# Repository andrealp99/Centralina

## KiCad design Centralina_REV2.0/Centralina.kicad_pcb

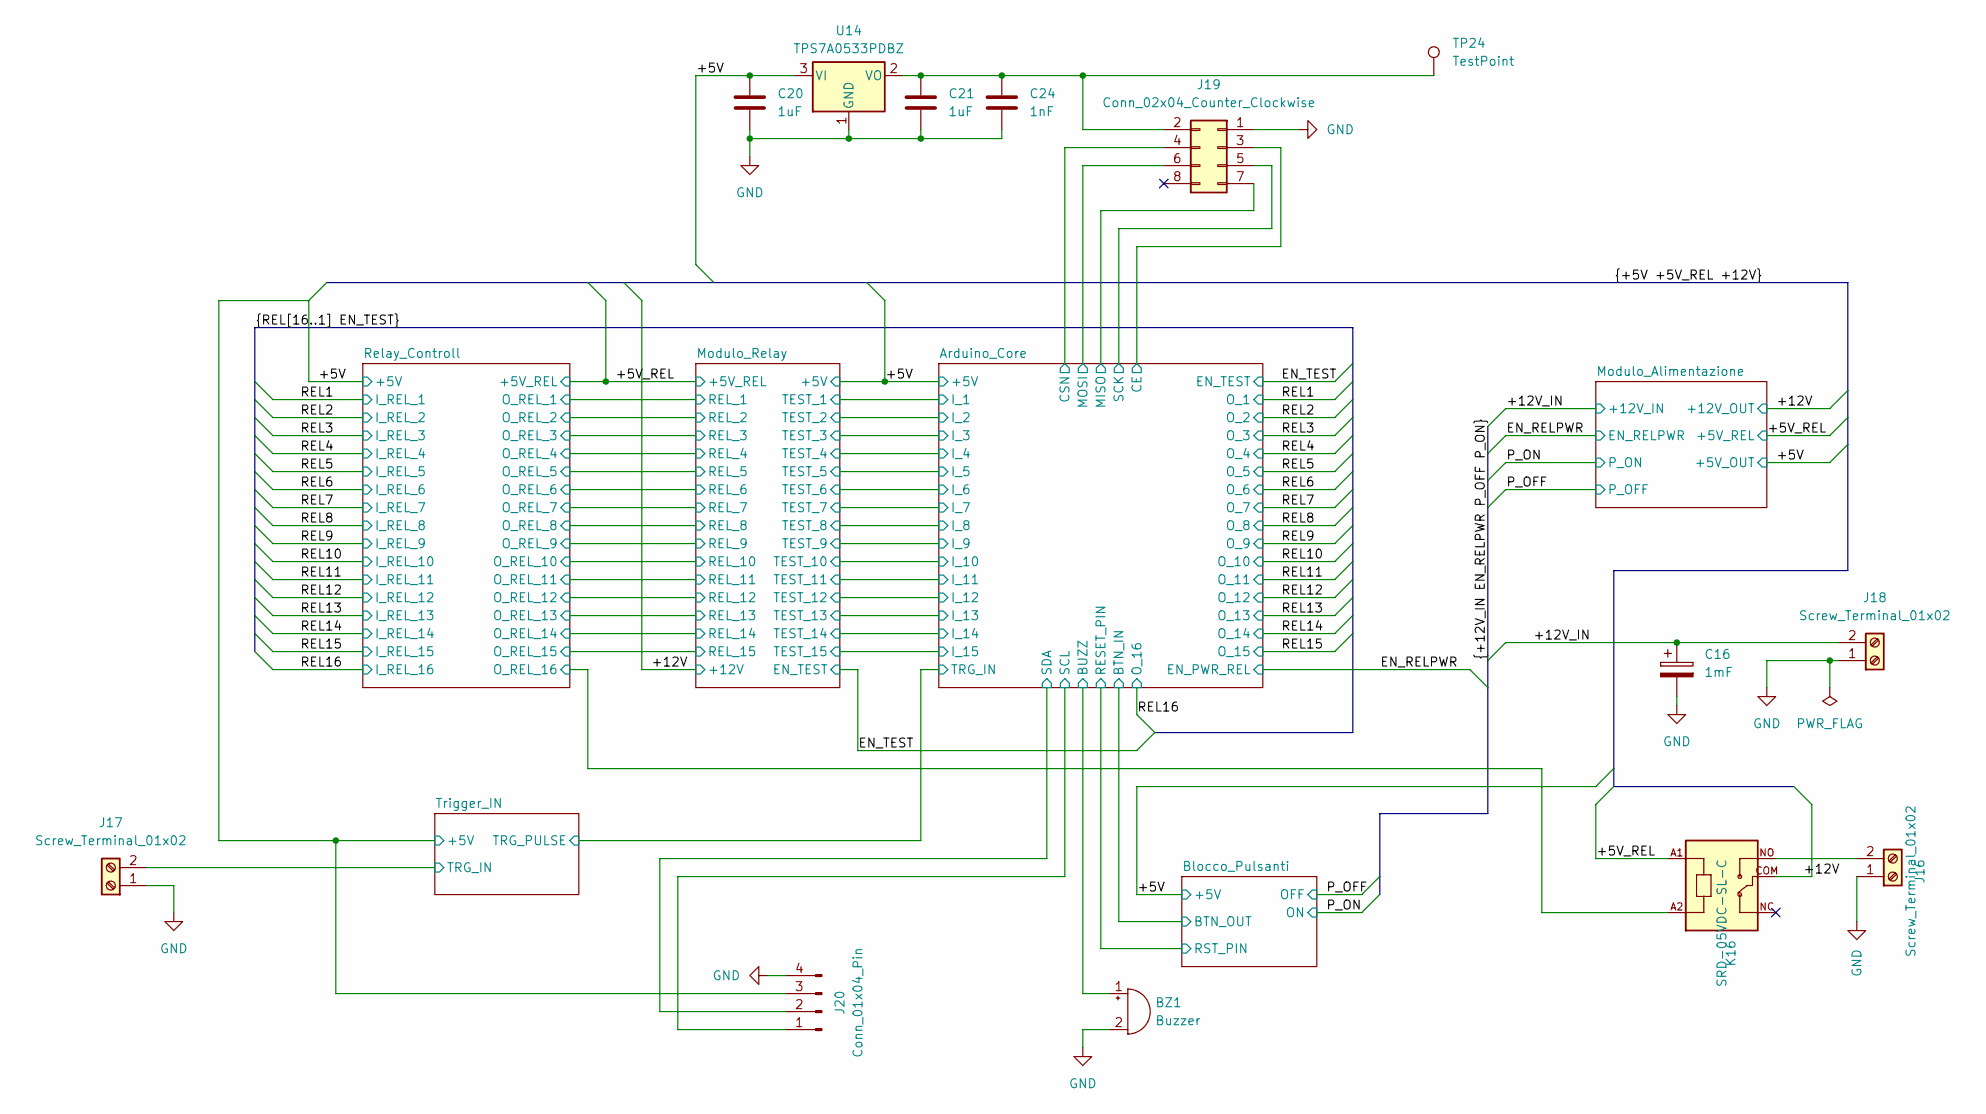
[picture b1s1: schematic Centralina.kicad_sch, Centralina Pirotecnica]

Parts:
BZ1: Buzzer; BUZ-TH_BD9.0-P4.00-D0.6-FD
C16: 1mF; CP_Radial_D10.0mm_P5.00mm
C20, C21: 1uF; C_0805_2012Metric
C24: 1nF; C_0805_2012Metric
J16, J17, J18: Screw_Terminal_01x02; mors_2p
J19: Conn_02x04_Counter_Clockwise; HDR-TH_8P-P2.54-V-F-R2-C4-S2.54
J20: Conn_01x04_Pin; HDR-TH_4P-P2.54-H-F-W10.2
K16: SRD-05VDC-SL-C; RELAY_SRD-05VDC-SL-C
TP24: TestPoint; TestPoint_Pad_D1.0mm
U14: TPS7A0533PDBZ; SOT-23

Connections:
/+5V: C20.1, J20.3, U14.3 (VI); also elsewhere on the board
/+5V_REL: K16.A1; also elsewhere on the board
/+12V: K16.COM; also elsewhere on the board
/+12V_IN: C16.1, J18.2; also elsewhere on the board
/Arduino_Core/BUZZ: BZ1.1 (+); also elsewhere on the board
/Arduino_Core/CE: J19.3 (Pin_2); also elsewhere on the board
/Arduino_Core/CSN: J19.4 (Pin_7); also elsewhere on the board
/Arduino_Core/MISO: J19.7 (Pin_4); also elsewhere on the board
/Arduino_Core/MOSI: J19.6; also elsewhere on the board
/Arduino_Core/SCK: J19.5 (Pin_3); also elsewhere on the board
/Arduino_Core/SCL: J20.1; also elsewhere on the board
/Arduino_Core/SDA: J20.2; also elsewhere on the board
/Relay_Controll/O_REL_16: K16.A2; also elsewhere on the board
/Trigger_IN/TRG_IN: J17.2; also elsewhere on the board
GND: BZ1.2 (-), C16.2, C20.2, C21.2, C24.2, J16.1, J17.1, J18.1, J19.1, J20.4, U14.1 (GND); also elsewhere on the board
unnamed: J16.2, K16.NO
unnamed: C21.1, C24.1, J19.2 (Pin_8), TP24.1, U14.2 (VO)

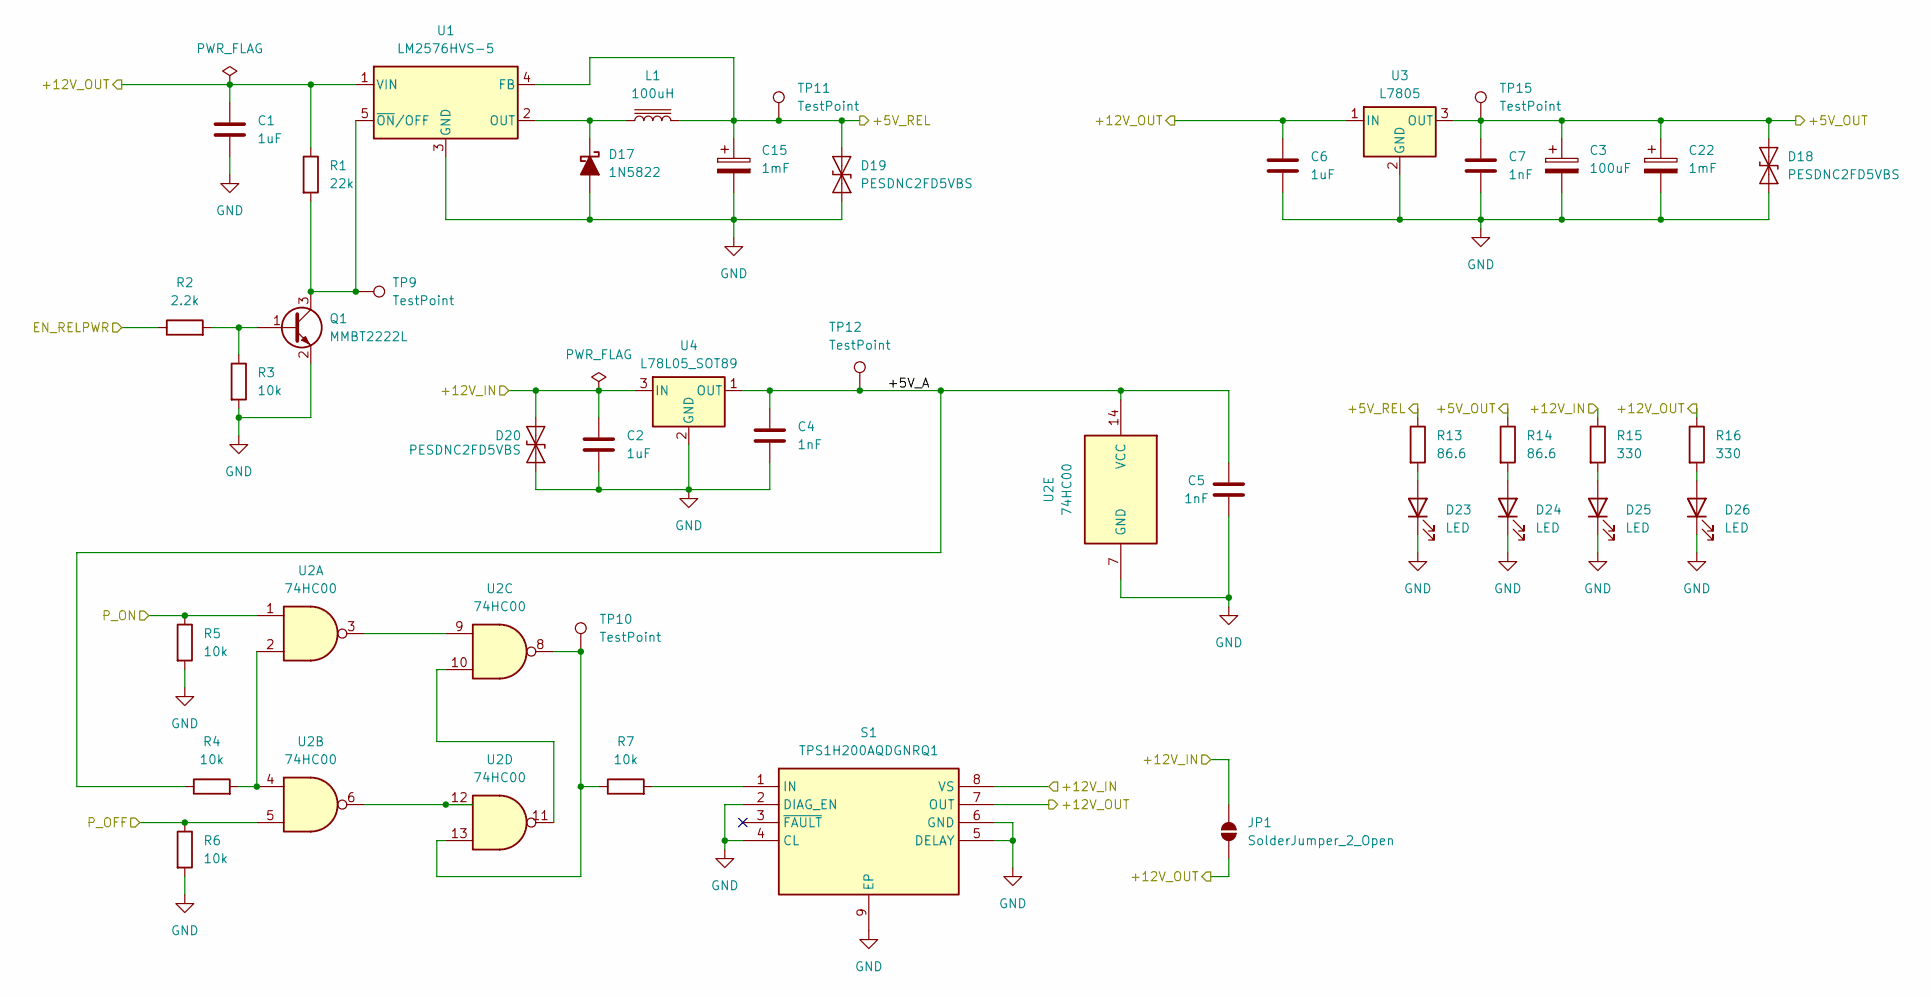
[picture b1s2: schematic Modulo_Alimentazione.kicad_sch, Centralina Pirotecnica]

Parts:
C1, C2, C6: 1uF; C_0805_2012Metric
C3: 100uF; CP_Radial_D5.0mm_P2.00mm
C4, C5, C7: 1nF; C_0805_2012Metric
C15, C22: 1mF; CP_Radial_D10.0mm_P5.00mm
D17: 1N5822; D_SOD-323
D18, D19, D20: PESDNC2FD5VBS; DIODFN100X60X40-2N
D23, D24, D25, D26: LED; LED_0805_2012Metric
JP1: SolderJumper_2_Open; SolderJumper-2_P1.3mm_Open_RoundedPad1.0x1.5mm
L1: 100uH; IND-TH_BD13.0-P6.00-D0.8
Q1: MMBT2222L; SOT-23
R1: 22k; R_0805_2012Metric
R2: 2.2k; R_0805_2012Metric
R3, R4, R5, R6, R7: 10k; R_0805_2012Metric
R13, R14: 86.6; R_0805_2012Metric
R15, R16: 330; R_0805_2012Metric
S1: TPS1H200AQDGNRQ1; SOP65P490X110-9N; Mouser Part Number 595-TPS1H200AQDGNRQ1
TP9, TP10, TP11, TP12, TP15: TestPoint; TestPoint_Pad_D1.0mm
U1: LM2576HVS-5; TO-263-5_TabPin3
U2: 74HC00; SOIC-14_3.9x8.7mm_P1.27mm
U3: L7805; TO-263-2
U4: L78L05_SOT89; SOT-89-3

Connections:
/+5V: C3.1, C7.1, C22.1, D18.2 (A2), R14.1, TP15.1, U3.3 (OUT); also elsewhere on the board
/+5V_REL: C15.1, D19.2 (A2), L1.2, R13.1, TP11.1, U1.4 (FB); also elsewhere on the board
/+12V: C1.1, C6.1, JP1.1 (A), R1.1, R16.1, S1.7 (OUT), U1.1 (VIN), U3.1 (IN); also elsewhere on the board
/+12V_IN: C2.1, D20.2 (A2), JP1.2 (B), R15.1, S1.8 (VS), U4.3 (IN); also elsewhere on the board
/EN_RELPWR: R2.1; also elsewhere on the board
/Modulo_Alimentazione/+5V_A: C4.1, C5.1, R4.1, TP12.1, U2.14 (VCC), U4.1 (OUT)
/P_OFF: R6.1, U2.5; also elsewhere on the board
/P_ON: R5.1, U2.1; also elsewhere on the board
GND: C1.2, C2.2, C3.2, C4.2, C5.2, C6.2, C7.2, C15.2, C22.2, D17.2 (A), D18.1 (A1), D19.1 (A1), D20.1 (A1), D23.1 (K), D24.1 (K), D25.1 (K), D26.1 (K), Q1.2 (E), R3.2, R5.2, R6.2, S1.2 (DIAG_EN), S1.4 (CL), S1.5 (DELAY), S1.6 (GND), S1.9 (EP), U1.3 (GND), U2.7 (GND), U3.2 (GND), U4.2 (GND); also elsewhere on the board
unnamed: D17.1 (K), L1.1, U1.2 (OUT)
unnamed: D23.2 (A), R13.2
unnamed: D24.2 (A), R14.2
unnamed: D25.2 (A), R15.2
unnamed: D26.2 (A), R16.2
unnamed: Q1.1 (B), R2.2, R3.1
unnamed: Q1.3 (C), R1.2, TP9.1, U1.5 (~ON/OFF)
unnamed: R4.2, U2.2, U2.4
unnamed: R7.1, TP10.1, U2.8, U2.13
unnamed: R7.2, S1.1 (IN)
unnamed: U2.3, U2.9
unnamed: U2.10, U2.11
unnamed: U2.6, U2.12

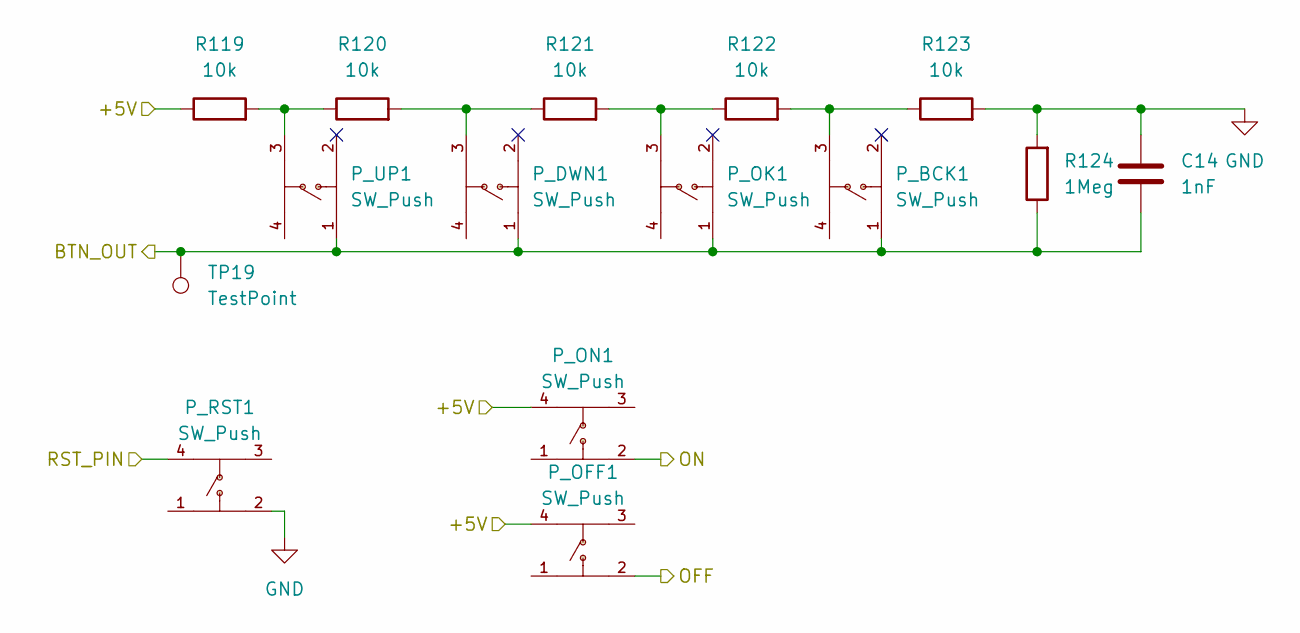
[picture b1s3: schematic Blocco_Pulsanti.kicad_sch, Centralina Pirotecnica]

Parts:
C14: 1nF; C_0805_2012Metric
P_BCK1: SW_Push; KEY-SMD_4P-L12.0-W12.0-P5.00-LS15.2; LCSC C2834980
P_DWN1: SW_Push; KEY-SMD_4P-L12.0-W12.0-P5.00-LS15.2; LCSC C2834980
P_OFF1: SW_Push; KEY-SMD_4P-L12.0-W12.0-P5.00-LS15.2; LCSC C2834980
P_OK1: SW_Push; KEY-SMD_4P-L12.0-W12.0-P5.00-LS15.2; LCSC C2834980
P_ON1: SW_Push; KEY-SMD_4P-L12.0-W12.0-P5.00-LS15.2; LCSC C2834980
P_RST1: SW_Push; KEY-SMD_4P-L12.0-W12.0-P5.00-LS15.2; LCSC C2834980
P_UP1: SW_Push; KEY-SMD_4P-L12.0-W12.0-P5.00-LS15.2; LCSC C2834980
R119, R120, R121, R122, R123: 10k; R_0805_2012Metric
R124: 1Meg; R_0805_2012Metric
TP19: TestPoint; TestPoint_Pad_D1.0mm

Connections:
/+5V: P_OFF1.4, P_ON1.4, R119.1; also elsewhere on the board
/Arduino_Core/BTN_IN: C14.2, P_BCK1.1, P_DWN1.1, P_OK1.1, P_UP1.1, R124.1, TP19.1; also elsewhere on the board
/Arduino_Core/RESET_PIN: P_RST1.4; also elsewhere on the board
/P_OFF: P_OFF1.2; also elsewhere on the board
/P_ON: P_ON1.2; also elsewhere on the board
GND: C14.1, P_RST1.2, R123.2, R124.2; also elsewhere on the board
unnamed: P_BCK1.3, R122.2, R123.1
unnamed: P_DWN1.3, R120.2, R121.1
unnamed: P_OK1.3, R121.2, R122.1
unnamed: P_UP1.3, R119.2, R120.1

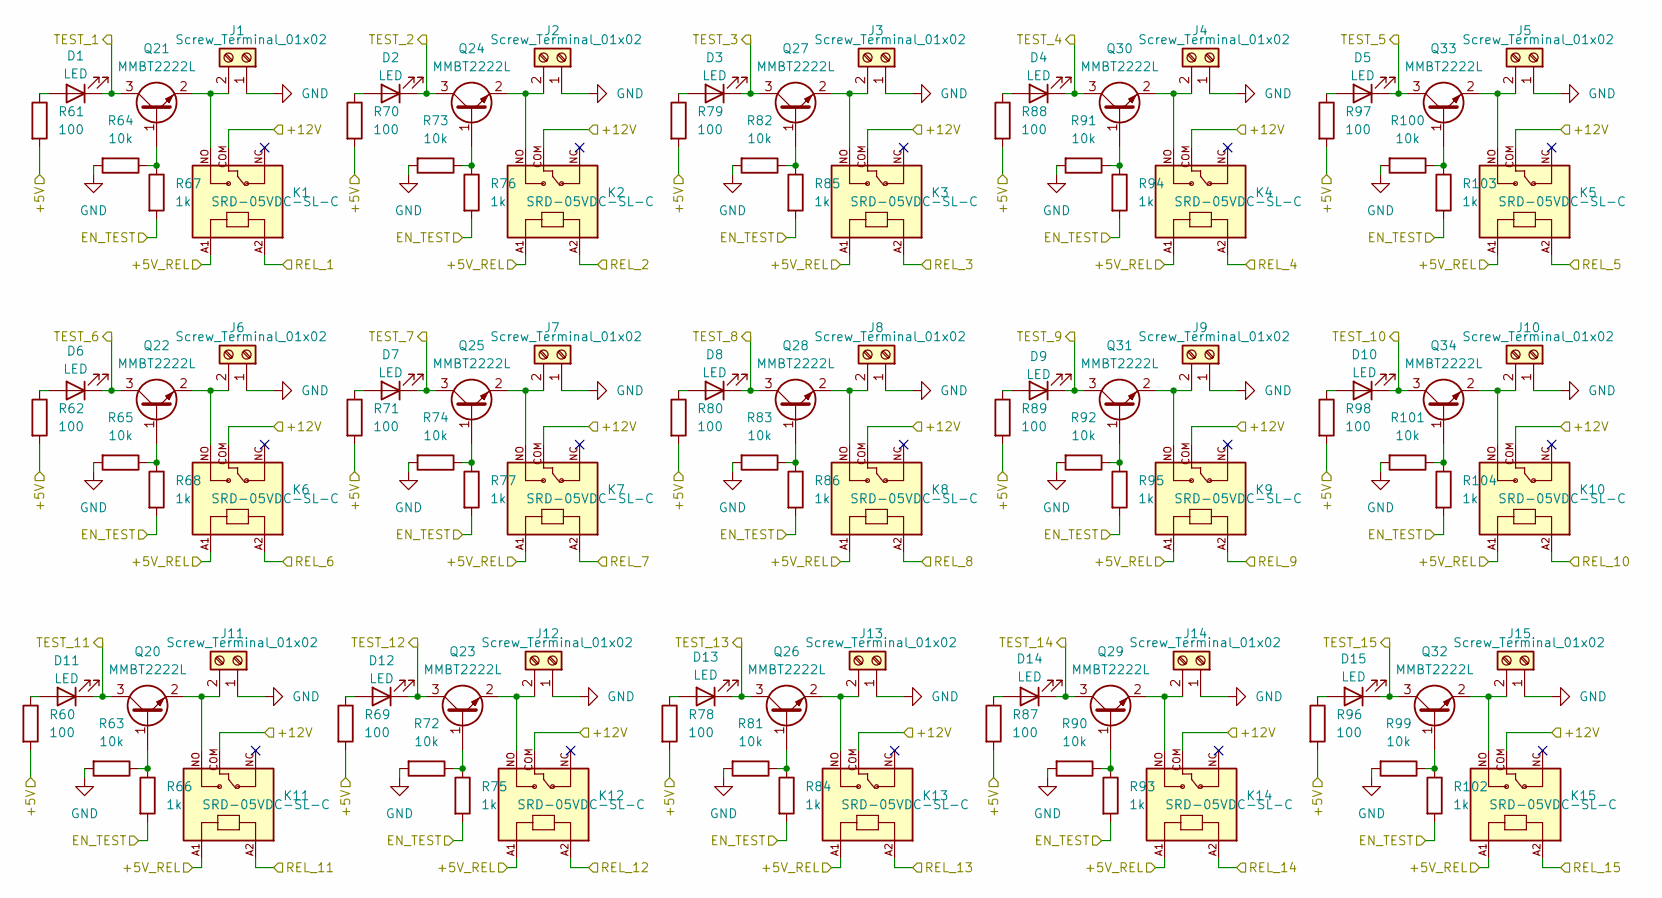
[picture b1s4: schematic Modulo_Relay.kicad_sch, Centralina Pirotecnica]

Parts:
D1, D2, D3, D4, D5, D6, D7, D8, D9, D10, D11, D12, D13, D14, D15: LED; LED_0805_2012Metric
J1, J2, J3, J4, J5, J6, J7, J8, J9, J10, J11, J12, J13, J14, J15: Screw_Terminal_01x02; mors_2p
K1, K2, K3, K4, K5, K6, K7, K8, K9, K10, K11, K12, K13, K14, K15: SRD-05VDC-SL-C; RELAY_SRD-05VDC-SL-C
Q20, Q21, Q22, Q23, Q24, Q25, Q26, Q27, Q28, Q29, Q30, Q31, Q32, Q33, Q34: MMBT2222L; SOT-23
R60, R61, R62, R69, R70, R71, R78, R79, R80, R87, R88, R89, R96, R97, R98: 100; R_0805_2012Metric
R63, R64, R65, R72, R73, R74, R81, R82, R83, R90, R91, R92, R99, R100, R101: 10k; R_0805_2012Metric
R66, R67, R68, R75, R76, R77, R84, R85, R86, R93, R94, R95, R102, R103, R104: 1k; R_0805_2012Metric

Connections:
/+5V: R60.2, R61.2, R62.2, R69.2, R70.2, R71.2, R78.2, R79.2, R80.2, R87.2, R88.2, R89.2, R96.2, R97.2, R98.2; also elsewhere on the board
/+5V_REL: K1.A1, K2.A1, K3.A1, K4.A1, K5.A1, K6.A1, K7.A1, K8.A1, K9.A1, K10.A1, K11.A1, K12.A1, K13.A1, K14.A1, K15.A1; also elsewhere on the board
/+12V: K1.COM, K2.COM, K3.COM, K4.COM, K5.COM, K6.COM, K7.COM, K8.COM, K9.COM, K10.COM, K11.COM, K12.COM, K13.COM, K14.COM, K15.COM; also elsewhere on the board
/Arduino_Core/I_1: D1.1 (K), Q21.3 (C); also elsewhere on the board
/Arduino_Core/I_2: D2.1 (K), Q24.3 (C); also elsewhere on the board
/Arduino_Core/I_3: D3.1 (K), Q27.3 (C); also elsewhere on the board
/Arduino_Core/I_4: D4.1 (K), Q30.3 (C); also elsewhere on the board
/Arduino_Core/I_5: D5.1 (K), Q33.3 (C); also elsewhere on the board
/Arduino_Core/I_6: D6.1 (K), Q22.3 (C); also elsewhere on the board
/Arduino_Core/I_7: D7.1 (K), Q25.3 (C); also elsewhere on the board
/Arduino_Core/I_8: D8.1 (K), Q28.3 (C); also elsewhere on the board
/Arduino_Core/I_9: D9.1 (K), Q31.3 (C); also elsewhere on the board
/Arduino_Core/I_10: D10.1 (K), Q34.3 (C); also elsewhere on the board
/Arduino_Core/I_11: D11.1 (K), Q20.3 (C); also elsewhere on the board
/Arduino_Core/I_12: D12.1 (K), Q23.3 (C); also elsewhere on the board
/Arduino_Core/I_13: D13.1 (K), Q26.3 (C); also elsewhere on the board
/Arduino_Core/I_14: D14.1 (K), Q29.3 (C); also elsewhere on the board
/Arduino_Core/I_15: D15.1 (K), Q32.3 (C); also elsewhere on the board
/EN_TEST: R66.2, R67.2, R68.2, R75.2, R76.2, R77.2, R84.2, R85.2, R86.2, R93.2, R94.2, R95.2, R102.2, R103.2, R104.2; also elsewhere on the board
/Modulo_Relay/REL_1: K1.A2; also elsewhere on the board
/Modulo_Relay/REL_2: K2.A2; also elsewhere on the board
/Modulo_Relay/REL_3: K3.A2; also elsewhere on the board
/Modulo_Relay/REL_4: K4.A2; also elsewhere on the board
/Modulo_Relay/REL_5: K5.A2; also elsewhere on the board
/Modulo_Relay/REL_6: K6.A2; also elsewhere on the board
/Modulo_Relay/REL_7: K7.A2; also elsewhere on the board
/Modulo_Relay/REL_8: K8.A2; also elsewhere on the board
/Modulo_Relay/REL_9: K9.A2; also elsewhere on the board
/Modulo_Relay/REL_10: K10.A2; also elsewhere on the board
/Modulo_Relay/REL_11: K11.A2; also elsewhere on the board
/Modulo_Relay/REL_12: K12.A2; also elsewhere on the board
/Modulo_Relay/REL_13: K13.A2; also elsewhere on the board
/Modulo_Relay/REL_14: K14.A2; also elsewhere on the board
/Modulo_Relay/REL_15: K15.A2; also elsewhere on the board
GND: J1.1, J2.1, J3.1, J4.1, J5.1, J6.1, J7.1, J8.1, J9.1, J10.1, J11.1, J12.1, J13.1, J14.1, J15.1, R63.2, R64.2, R65.2, R72.2, R73.2, R74.2, R81.2, R82.2, R83.2, R90.2, R91.2, R92.2, R99.2, R100.2, R101.2; also elsewhere on the board
unnamed: D1.2 (A), R61.1
unnamed: D2.2 (A), R70.1
unnamed: D3.2 (A), R79.1
unnamed: D4.2 (A), R88.1
unnamed: D5.2 (A), R97.1
unnamed: D6.2 (A), R62.1
unnamed: D7.2 (A), R71.1
unnamed: D8.2 (A), R80.1
unnamed: D9.2 (A), R89.1
unnamed: D10.2 (A), R98.1
unnamed: D11.2 (A), R60.1
unnamed: D12.2 (A), R69.1
unnamed: D13.2 (A), R78.1
unnamed: D14.2 (A), R87.1
unnamed: D15.2 (A), R96.1
unnamed: J1.2, K1.NO, Q21.2 (E)
unnamed: J2.2, K2.NO, Q24.2 (E)
unnamed: J3.2, K3.NO, Q27.2 (E)
unnamed: J4.2, K4.NO, Q30.2 (E)
unnamed: J5.2, K5.NO, Q33.2 (E)
unnamed: J6.2, K6.NO, Q22.2 (E)
unnamed: J7.2, K7.NO, Q25.2 (E)
unnamed: J8.2, K8.NO, Q28.2 (E)
unnamed: J9.2, K9.NO, Q31.2 (E)
unnamed: J10.2, K10.NO, Q34.2 (E)
unnamed: J11.2, K11.NO, Q20.2 (E)
unnamed: J12.2, K12.NO, Q23.2 (E)
unnamed: J13.2, K13.NO, Q26.2 (E)
unnamed: J14.2, K14.NO, Q29.2 (E)
unnamed: J15.2, K15.NO, Q32.2 (E)
unnamed: Q20.1 (B), R63.1, R66.1
unnamed: Q21.1 (B), R64.1, R67.1
unnamed: Q22.1 (B), R65.1, R68.1
unnamed: Q23.1 (B), R72.1, R75.1
unnamed: Q24.1 (B), R73.1, R76.1
unnamed: Q25.1 (B), R74.1, R77.1
unnamed: Q26.1 (B), R81.1, R84.1
unnamed: Q27.1 (B), R82.1, R85.1
unnamed: Q28.1 (B), R83.1, R86.1
unnamed: Q29.1 (B), R90.1, R93.1
unnamed: Q30.1 (B), R91.1, R94.1
unnamed: Q31.1 (B), R92.1, R95.1
unnamed: Q32.1 (B), R99.1, R102.1
unnamed: Q33.1 (B), R100.1, R103.1
unnamed: Q34.1 (B), R101.1, R104.1

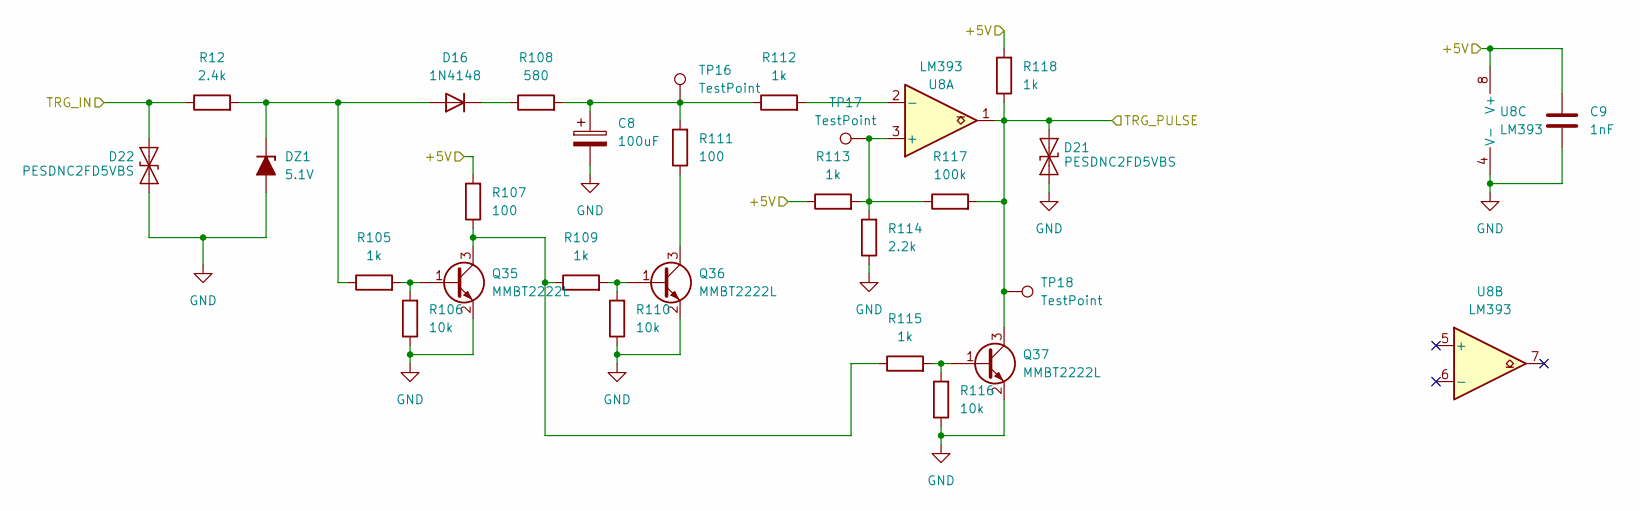
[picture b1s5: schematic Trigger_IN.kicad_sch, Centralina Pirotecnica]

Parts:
C8: 100uF; CP_Elec_6.3x7.7
C9: 1nF; C_0805_2012Metric
D16: 1N4148; D_SOD-323
D21, D22: PESDNC2FD5VBS; DIODFN100X60X40-2N
DZ1: 5.1V; D_MiniMELF
Q35, Q36, Q37: MMBT2222L; SOT-23
R12: 2.4k; R_0805_2012Metric
R105, R109, R112, R113, R115, R118: 1k; R_0805_2012Metric
R106, R110, R116: 10k; R_0805_2012Metric
R107, R111: 100; R_0805_2012Metric
R108: 580; RES-TH_BD1.9-L3.3-P7.30-D0.5
R114: 2.2k; R_0805_2012Metric
R117: 100k; R_0805_2012Metric
TP16, TP17, TP18: TestPoint; TestPoint_Pad_D1.0mm
U8: LM393; SOIC127P599X175-8N

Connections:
/+5V: C9.1, R107.2, R113.1, R118.2, U8.8 (V+); also elsewhere on the board
/Arduino_Core/TRG_IN: D21.2 (A2), Q37.3 (C), R117.2, R118.1, TP18.1, U8.1; also elsewhere on the board
/Trigger_IN/TRG_IN: D22.2 (A2), R12.1; also elsewhere on the board
GND: C8.2, C9.2, D21.1 (A1), D22.1 (A1), DZ1.2 (A), Q35.2 (E), Q36.2 (E), Q37.2 (E), R106.1, R110.1, R114.1, R116.1, U8.4 (V-); also elsewhere on the board
unnamed: C8.1, R108.2, R111.2, R112.1, TP16.1
unnamed: D16.2 (A), DZ1.1 (K), R12.2, R105.1
unnamed: D16.1 (K), R108.1
unnamed: Q35.1 (B), R105.2, R106.2
unnamed: Q35.3 (C), R107.1, R109.1, R115.1
unnamed: Q36.1 (B), R109.2, R110.2
unnamed: Q36.3 (C), R111.1
unnamed: Q37.1 (B), R115.2, R116.2
unnamed: R113.2, R114.2, R117.1, TP17.1, U8.3 (+)
unnamed: R112.2, U8.2 (-)

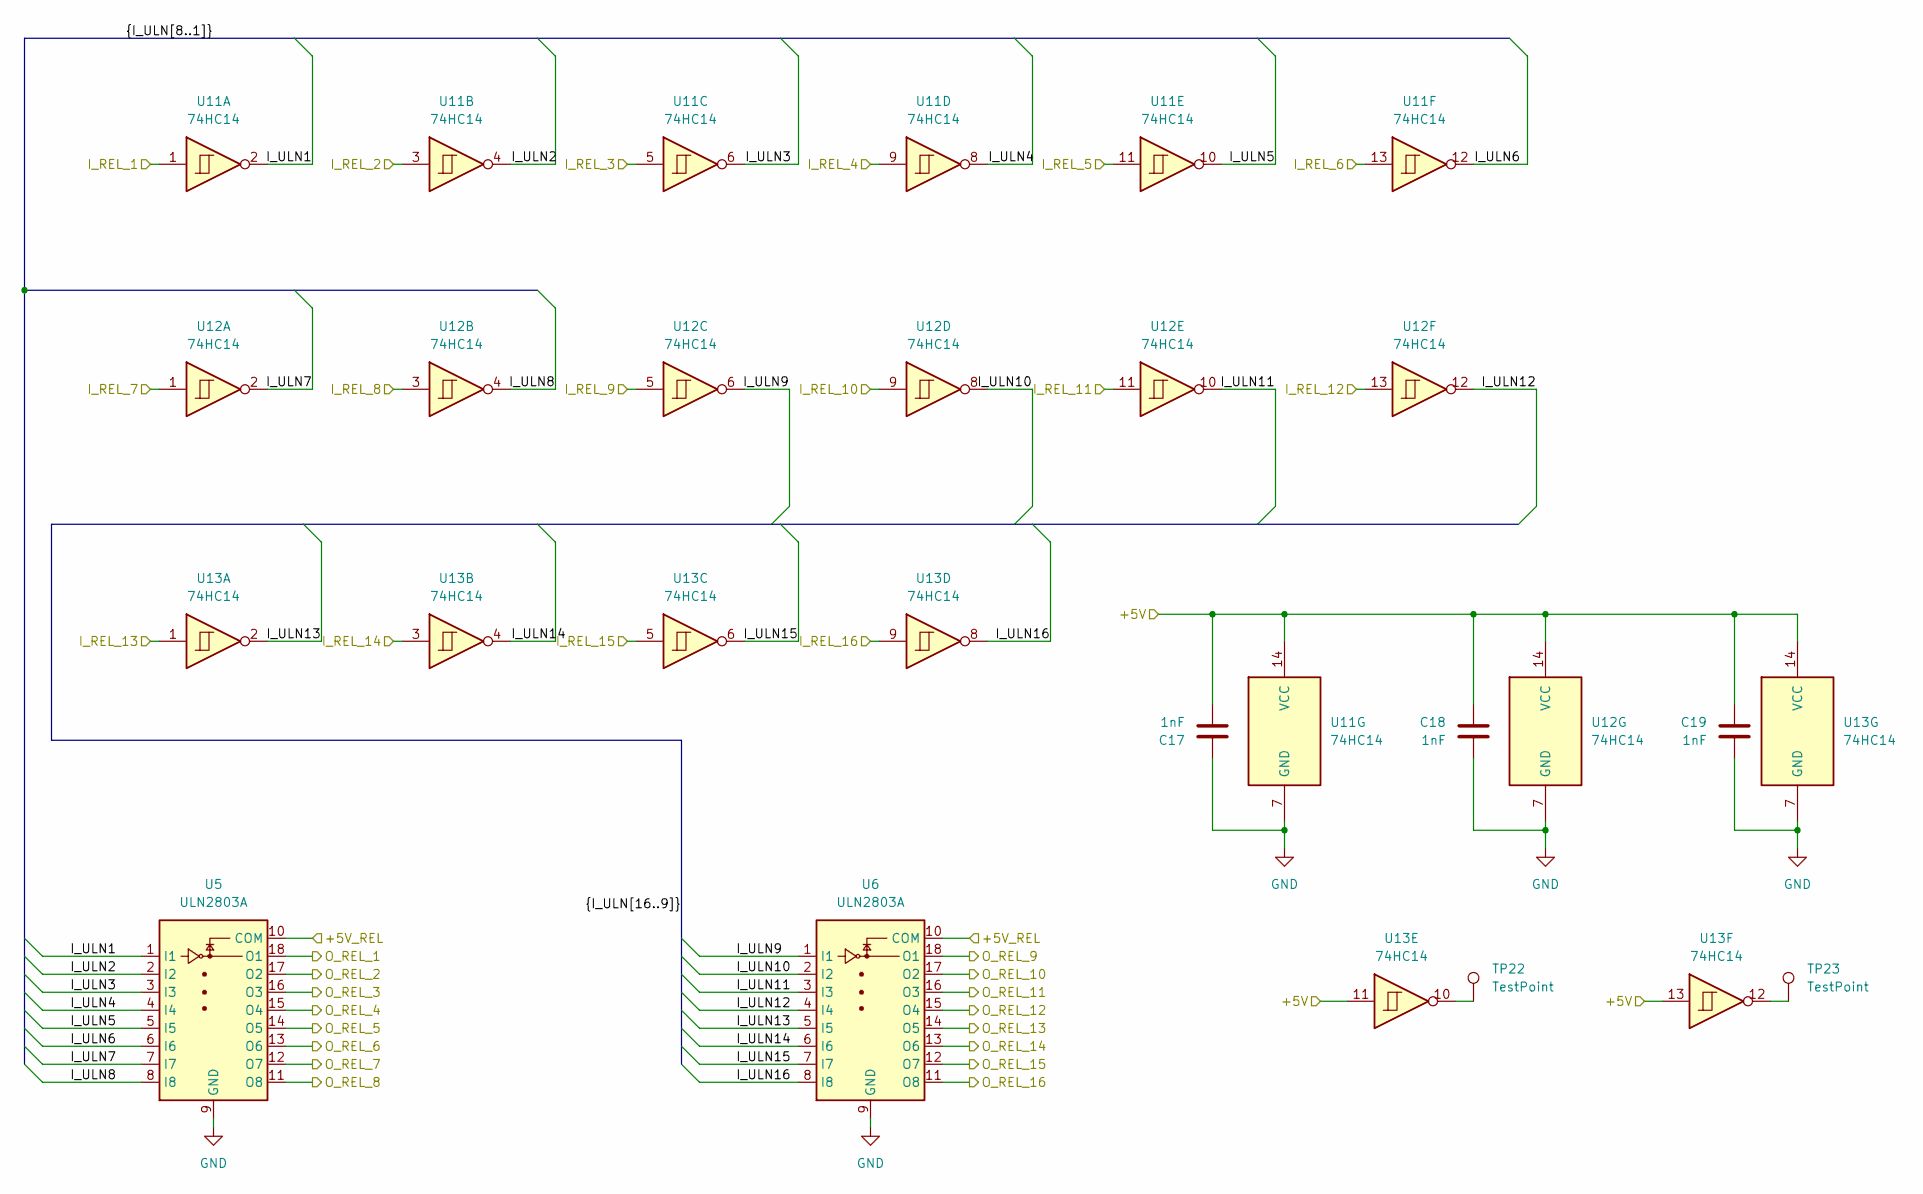
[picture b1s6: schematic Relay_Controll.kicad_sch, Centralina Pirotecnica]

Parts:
C17, C18, C19: 1nF; C_0805_2012Metric
TP22, TP23: TestPoint; TestPoint_Pad_D1.0mm
U5, U6: ULN2803A; SOIC127P1030X265-18N
U11, U12, U13: 74HC14; SOIC-14_3.9x8.7mm_P1.27mm

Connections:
/+5V: C17.2, C18.2, C19.2, U11.14 (VCC), U12.14 (VCC), U13.11, U13.13, U13.14 (VCC); also elsewhere on the board
/+5V_REL: U5.10 (COM), U6.10 (COM); also elsewhere on the board
/Modulo_Relay/REL_1: U5.18 (O1); also elsewhere on the board
/Modulo_Relay/REL_2: U5.17 (O2); also elsewhere on the board
/Modulo_Relay/REL_3: U5.16 (O3); also elsewhere on the board
/Modulo_Relay/REL_4: U5.15 (O4); also elsewhere on the board
/Modulo_Relay/REL_5: U5.14 (O5); also elsewhere on the board
/Modulo_Relay/REL_6: U5.13 (O6); also elsewhere on the board
/Modulo_Relay/REL_7: U5.12 (O7); also elsewhere on the board
/Modulo_Relay/REL_8: U5.11 (O8); also elsewhere on the board
/Modulo_Relay/REL_9: U6.18 (O1); also elsewhere on the board
/Modulo_Relay/REL_10: U6.17 (O2); also elsewhere on the board
/Modulo_Relay/REL_11: U6.16 (O3); also elsewhere on the board
/Modulo_Relay/REL_12: U6.15 (O4); also elsewhere on the board
/Modulo_Relay/REL_13: U6.14 (O5); also elsewhere on the board
/Modulo_Relay/REL_14: U6.13 (O6); also elsewhere on the board
/Modulo_Relay/REL_15: U6.12 (O7); also elsewhere on the board
/REL1: U11.1; also elsewhere on the board
/REL2: U11.3; also elsewhere on the board
/REL3: U11.5; also elsewhere on the board
/REL4: U11.9; also elsewhere on the board
/REL5: U11.11; also elsewhere on the board
/REL6: U11.13; also elsewhere on the board
/REL7: U12.1; also elsewhere on the board
/REL8: U12.3; also elsewhere on the board
/REL9: U12.5; also elsewhere on the board
/REL10: U12.9; also elsewhere on the board
/REL11: U12.11; also elsewhere on the board
/REL12: U12.13; also elsewhere on the board
/REL13: U13.1; also elsewhere on the board
/REL14: U13.3; also elsewhere on the board
/REL15: U13.5; also elsewhere on the board
/REL16: U13.9; also elsewhere on the board
/Relay_Controll/I_ULN1: U5.1 (I1), U11.2
/Relay_Controll/I_ULN2: U5.2 (I2), U11.4
/Relay_Controll/I_ULN3: U5.3 (I3), U11.6
/Relay_Controll/I_ULN4: U5.4 (I4), U11.8
/Relay_Controll/I_ULN5: U5.5 (I5), U11.10
/Relay_Controll/I_ULN6: U5.6 (I6), U11.12
/Relay_Controll/I_ULN7: U5.7 (I7), U12.2
/Relay_Controll/I_ULN8: U5.8 (I8), U12.4
/Relay_Controll/I_ULN9: U6.1 (I1), U12.6
/Relay_Controll/I_ULN10: U6.2 (I2), U12.8
/Relay_Controll/I_ULN11: U6.3 (I3), U12.10
/Relay_Controll/I_ULN12: U6.4 (I4), U12.12
/Relay_Controll/I_ULN13: U6.5 (I5), U13.2
/Relay_Controll/I_ULN14: U6.6 (I6), U13.4
/Relay_Controll/I_ULN15: U6.7 (I7), U13.6
/Relay_Controll/I_ULN16: U6.8 (I8), U13.8
/Relay_Controll/O_REL_16: U6.11 (O8); also elsewhere on the board
GND: C17.1, C18.1, C19.1, U5.9 (GND), U6.9 (GND), U11.7 (GND), U12.7 (GND), U13.7 (GND); also elsewhere on the board
unnamed: TP22.1, U13.10
unnamed: TP23.1, U13.12

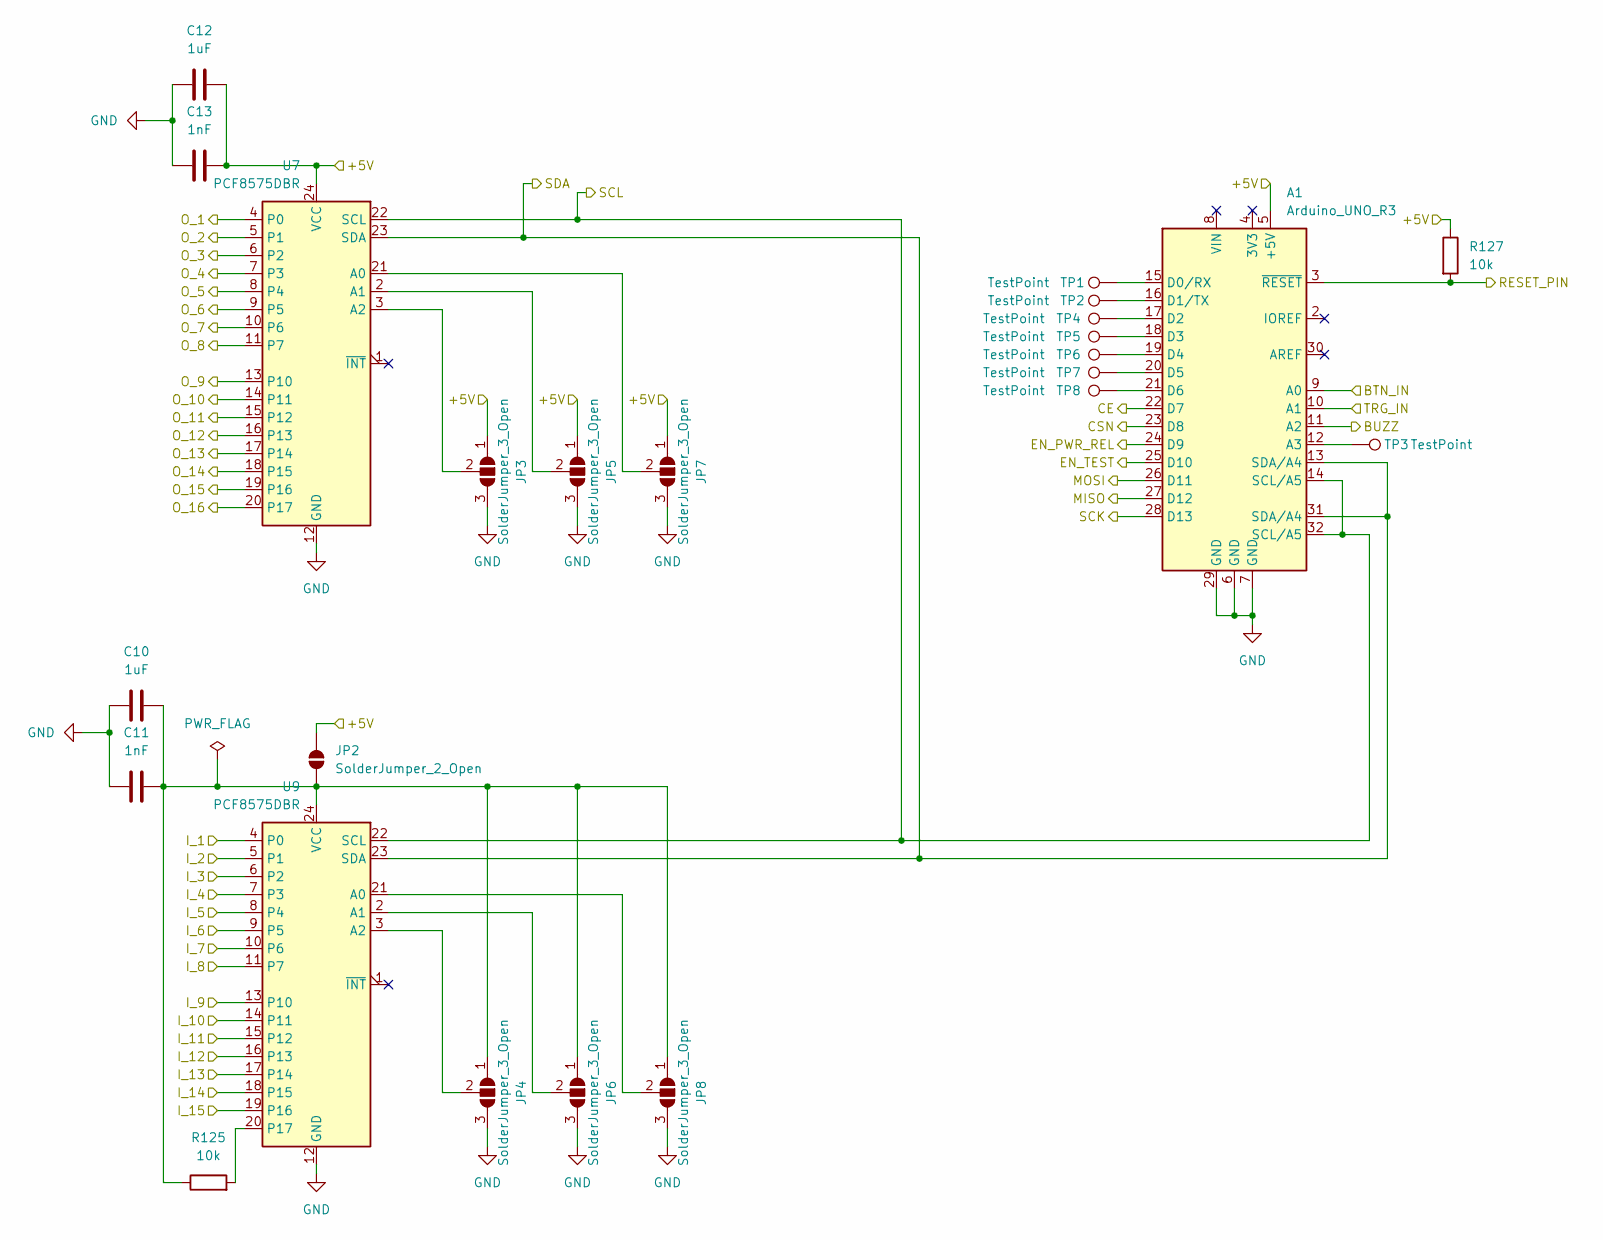
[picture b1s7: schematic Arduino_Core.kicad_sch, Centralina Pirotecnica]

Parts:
A1: Arduino_UNO_R3
C10, C12: 1uF; C_0805_2012Metric
C11, C13: 1nF; C_0805_2012Metric
JP2: SolderJumper_2_Open; SolderJumper-2_P1.3mm_Open_RoundedPad1.0x1.5mm
JP3, JP4, JP5, JP6, JP7, JP8: SolderJumper_3_Open; SolderJumper-3_P1.3mm_Open_RoundedPad1.0x1.5mm_NumberLabels
R125, R127: 10k; R_0805_2012Metric
TP1, TP2, TP3, TP4, TP5, TP6, TP7, TP8: TestPoint; TestPoint_Pad_D1.0mm
U7, U9: PCF8575DBR; SSOP-24_5.3x8.2mm_P0.65mm

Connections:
/+5V: A1.5 (+5V), C12.1, C13.2, JP2.2 (B), JP3.1 (A), JP5.1 (A), JP7.1 (A), R127.1, U7.24 (VCC); also elsewhere on the board
/Arduino_Core/BTN_IN: A1.9 (A0); also elsewhere on the board
/Arduino_Core/BUZZ: A1.11 (A2); also elsewhere on the board
/Arduino_Core/CE: A1.22 (D7); also elsewhere on the board
/Arduino_Core/CSN: A1.23 (D8); also elsewhere on the board
/Arduino_Core/I_1: U9.4 (P0); also elsewhere on the board
/Arduino_Core/I_2: U9.5 (P1); also elsewhere on the board
/Arduino_Core/I_3: U9.6 (P2); also elsewhere on the board
/Arduino_Core/I_4: U9.7 (P3); also elsewhere on the board
/Arduino_Core/I_5: U9.8 (P4); also elsewhere on the board
/Arduino_Core/I_6: U9.9 (P5); also elsewhere on the board
/Arduino_Core/I_7: U9.10 (P6); also elsewhere on the board
/Arduino_Core/I_8: U9.11 (P7); also elsewhere on the board
/Arduino_Core/I_9: U9.13 (P10); also elsewhere on the board
/Arduino_Core/I_10: U9.14 (P11); also elsewhere on the board
/Arduino_Core/I_11: U9.15 (P12); also elsewhere on the board
/Arduino_Core/I_12: U9.16 (P13); also elsewhere on the board
/Arduino_Core/I_13: U9.17 (P14); also elsewhere on the board
/Arduino_Core/I_14: U9.18 (P15); also elsewhere on the board
/Arduino_Core/I_15: U9.19 (P16); also elsewhere on the board
/Arduino_Core/MISO: A1.27 (D12); also elsewhere on the board
/Arduino_Core/MOSI: A1.26 (D11); also elsewhere on the board
/Arduino_Core/RESET_PIN: A1.3 (~RESET), R127.2; also elsewhere on the board
/Arduino_Core/SCK: A1.28 (D13); also elsewhere on the board
/Arduino_Core/SCL: A1.14 (SCL/A5), A1.32 (SCL/A5), U7.22 (SCL), U9.22 (SCL); also elsewhere on the board
/Arduino_Core/SDA: A1.13 (SDA/A4), A1.31 (SDA/A4), U7.23 (SDA), U9.23 (SDA); also elsewhere on the board
/Arduino_Core/TRG_IN: A1.10 (A1); also elsewhere on the board
/EN_RELPWR: A1.24 (D9); also elsewhere on the board
/EN_TEST: A1.25 (D10); also elsewhere on the board
/REL1: U7.4 (P0); also elsewhere on the board
/REL2: U7.5 (P1); also elsewhere on the board
/REL3: U7.6 (P2); also elsewhere on the board
/REL4: U7.7 (P3); also elsewhere on the board
/REL5: U7.8 (P4); also elsewhere on the board
/REL6: U7.9 (P5); also elsewhere on the board
/REL7: U7.10 (P6); also elsewhere on the board
/REL8: U7.11 (P7); also elsewhere on the board
/REL9: U7.13 (P10); also elsewhere on the board
/REL10: U7.14 (P11); also elsewhere on the board
/REL11: U7.15 (P12); also elsewhere on the board
/REL12: U7.16 (P13); also elsewhere on the board
/REL13: U7.17 (P14); also elsewhere on the board
/REL14: U7.18 (P15); also elsewhere on the board
/REL15: U7.19 (P16); also elsewhere on the board
/REL16: U7.20 (P17); also elsewhere on the board
GND: A1.6 (GND), A1.7 (GND), A1.29 (GND), C10.2, C11.1, C12.2, C13.1, JP3.3 (B), JP4.3 (B), JP5.3 (B), JP6.3 (B), JP7.3 (B), JP8.3 (B), U7.12 (GND), U9.12 (GND); also elsewhere on the board
unnamed: A1.12 (A3), TP3.1
unnamed: A1.15 (D0/RX), TP1.1
unnamed: A1.16 (D1/TX), TP2.1
unnamed: A1.17 (D2), TP4.1
unnamed: A1.18 (D3), TP5.1
unnamed: A1.19 (D4), TP6.1
unnamed: A1.20 (D5), TP7.1
unnamed: A1.21 (D6), TP8.1
unnamed: C10.1, C11.2, JP2.1 (A), JP4.1 (A), JP6.1 (A), JP8.1 (A), R125.1, U9.24 (VCC)
unnamed: JP3.2 (C), U7.3 (A2)
unnamed: JP4.2 (C), U9.3 (A2)
unnamed: JP5.2 (C), U7.2 (A1)
unnamed: JP6.2 (C), U9.2 (A1)
unnamed: JP7.2 (C), U7.21 (A0)
unnamed: JP8.2 (C), U9.21 (A0)
unnamed: R125.2, U9.20 (P17)

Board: 2 copper layers, 240 parts (0 on the bottom side), 177 nets, no tracks yet.

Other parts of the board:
H_1, H_2, H_3, H_4: MountingHole_2.1mm
